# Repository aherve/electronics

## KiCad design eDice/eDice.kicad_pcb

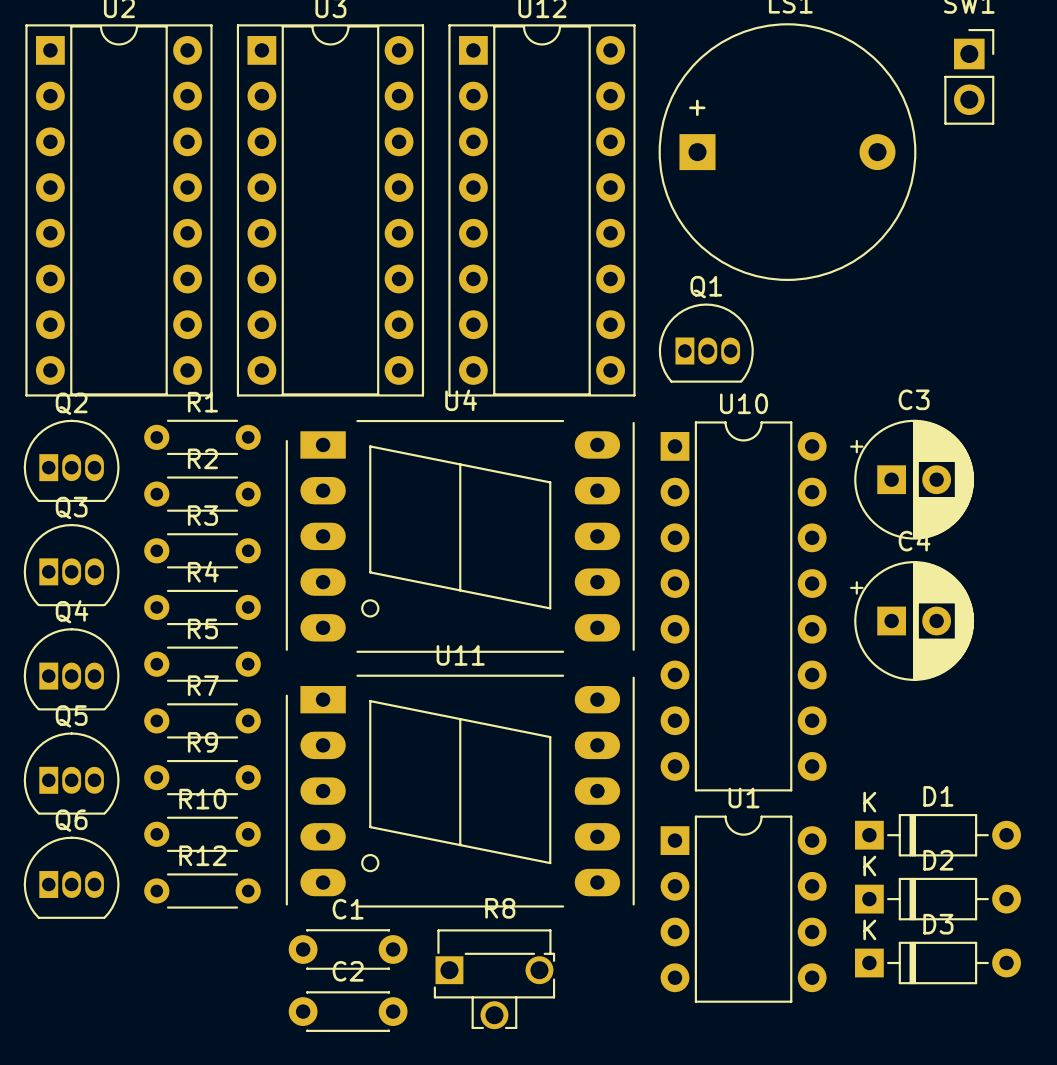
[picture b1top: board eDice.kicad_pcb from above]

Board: 2 copper layers, 32 parts (0 on the bottom side), 47 nets, no tracks yet.

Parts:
C1: 100nF; C_Disc_D4.3mm_W1.9mm_P5.00mm
C2: 10nF; C_Disc_D4.3mm_W1.9mm_P5.00mm
C3: C; CP_Radial_D6.3mm_P2.50mm
C4: C_Polarized; CP_Radial_D6.3mm_P2.50mm
D1, D2, D3: 1N4148; D_DO-35_SOD27_P7.62mm_Horizontal
LS1: buzzer; Buzzer_D14mm_H7mm_P10mm
Q1: PMOS; TO-92L_Inline
Q2, Q3, Q4, Q5, Q6: PN2222A; TO-92_Inline
R1, R2, R10: R; R_Axial_DIN0204_L3.6mm_D1.6mm_P5.08mm_Horizontal
R3: 1k; R_Axial_DIN0204_L3.6mm_D1.6mm_P5.08mm_Horizontal
R4, R5, R7, R9, R12: 10k; R_Axial_DIN0204_L3.6mm_D1.6mm_P5.08mm_Horizontal
R8: R_Variable; Potentiometer_Runtron_RM-063_Horizontal
SW1: SW_Push; PinSocket_1x02_P2.54mm_Vertical
U1: NE555P; DIP-8_W7.62mm
U2, U12: 4029; DIP-16_W7.62mm_Socket
U3: 4511; DIP-16_W7.62mm_Socket
U4, U11: SM420561N; 7SegmentLED_LTS6760_LTS6780
U10: 4511; DIP-16_W7.62mm

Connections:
GND: C1.2, C2.1, C3.2, C4.2, Q2.1 (E), R10.2, SW1.1, U1.1 (GND), U2.3 (J4), U2.4 (J1), U2.8 (VSS), U2.9 (B/D), U2.12 (J2), U2.13 (J3), U3.5 (~EL), U3.8 (Vss), U4.5 (DP), U10.5 (~EL), U10.8 (Vss), U11.5 (DP), U12.3 (J4), U12.5 (Cin), U12.8 (VSS), U12.9 (B/D), U12.12 (J2), U12.13 (J3)
unnamed: C3.1, R2.2, R3.1, SW1.2
unnamed: C4.1, LS1.2
unnamed: D1.1 (K), R2.1
unnamed: D2.2 (A), R7.1
unnamed: D2.1 (K), D3.1 (K)
unnamed: D3.2 (A), R9.1
unnamed: C1.1, Q1.1 (D), U1.2 (TR), U1.6 (THR)
unnamed: Q1.3 (S), R8.2, U1.7 (DIS)
unnamed: Q2.2 (B), R9.2
unnamed: Q2.3 (C), R1.2
unnamed: Q3.2 (B), R5.2
unnamed: Q3.3 (C), R4.2, U10.7 (DA), U12.6 (Q1)
unnamed: Q4.2 (B), R4.1
unnamed: Q4.3 (C), Q6.1 (E)
unnamed: Q4.1 (E), Q5.3 (C)
unnamed: Q5.2 (B), R7.2
unnamed: Q6.2 (B), R12.1
unnamed: Q6.3 (C), U10.6 (DD), U12.2 (Q4)
unnamed: R1.1, U4.3 (CC), U4.8 (CC)
unnamed: R10.1, U11.3 (CC), U11.8 (CC)
unnamed: C2.2, U1.5 (CV)
unnamed: U2.6 (Q1), U3.7 (DA)
unnamed: R5.1, U2.11 (Q2), U3.1 (DB)
unnamed: U2.14 (Q3), U3.2 (DC)
unnamed: U2.2 (Q4), U3.6 (DD)
unnamed: U3.13 (Qa), U4.7 (A)
unnamed: U3.12 (Qb), U4.6 (B)
unnamed: U3.11 (Qc), U4.4 (C)
unnamed: U3.10 (Qd), U4.2 (D)
unnamed: U3.9 (Qe), U4.1 (E)
unnamed: U3.15 (Qf), U4.9 (F)
unnamed: U3.14 (Qg), U4.10 (G)
unnamed: R12.2, U10.1 (DB), U12.11 (Q2)
unnamed: U10.2 (DC), U12.14 (Q3)
unnamed: U10.13 (Qa), U11.7 (A)
unnamed: U10.12 (Qb), U11.6 (B)
unnamed: U10.11 (Qc), U11.4 (C)
unnamed: U10.10 (Qd), U11.2 (D)
unnamed: U10.9 (Qe), U11.1 (E)
unnamed: U10.15 (Qf), U11.9 (F)
unnamed: U10.14 (Qg), U11.10 (G)
unnamed: U2.5 (Cin), U12.7 (Cout)
PE: Q3.1 (E), Q5.1 (E), U2.1 (PE), U12.1 (PE)
clck: D1.2 (A), LS1.1, U1.3 (Q), U2.15 (CK), U12.15 (CK)
fm: Q1.2 (G), R3.2
vcc: R8.1, U1.4 (R), U1.8 (VCC), U2.10 (U/D), U2.16 (VDD), U3.3 (~LT), U3.4 (~BI), U3.16 (Vdd), U10.3 (~LT), U10.4 (~BI), U10.16 (Vdd), U12.4 (J1), U12.10 (U/D), U12.16 (VDD)

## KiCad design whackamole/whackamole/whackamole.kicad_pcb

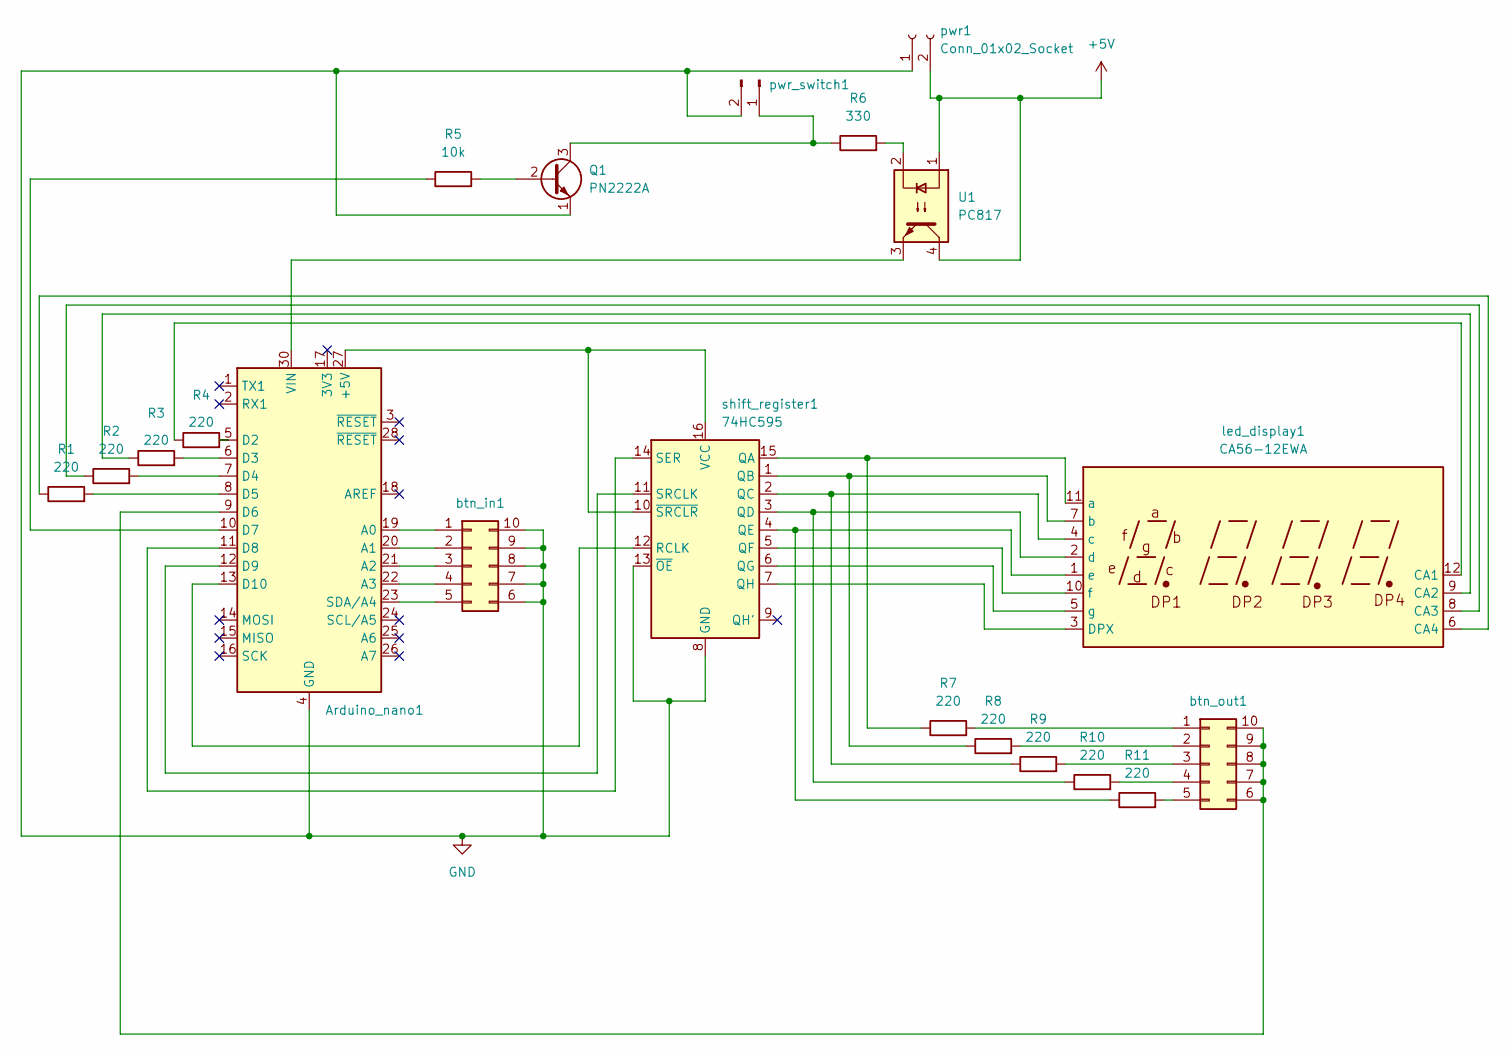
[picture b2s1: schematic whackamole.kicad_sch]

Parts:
Arduino_nano1: Arduino_Nano
Q1: PN2222A; TO-92
R1, R2, R3, R4, R7, R8, R9, R10, R11: 220; R_Axial_DIN0204_L3.6mm_D1.6mm_P1.90mm_Vertical
R5: 10k; R_Axial_DIN0207_L6.3mm_D2.5mm_P2.54mm_Vertical
R6: 330; R_Axial_DIN0204_L3.6mm_D1.6mm_P1.90mm_Vertical
U1: PC817; DIP-4_W7.62mm
btn_in1: PinHeader_2x05_P2.54mm_Vertical
btn_out1: PinHeader_2x05_P2.54mm_Vertical
led_display1: CA56-12EWA
pwr1: Conn_01x02_Socket; PinSocket_1x02_P1.27mm_Vertical
pwr_switch1: PinHeader_1x02_P2.54mm_Vertical
shift_register1: 74HC595; DIP-16_W7.62mm

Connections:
+5V: U1.1, U1.4, pwr1.2
GND: Arduino_nano1.4 (GND), Arduino_nano1.29 (GND), Q1.1 (E), btn_in1.6, btn_in1.7, btn_in1.8, btn_in1.9, btn_in1.10, pwr1.1, pwr_switch1.2, shift_register1.8 (GND), shift_register1.13 (~OE)
unnamed: Arduino_nano1.27 (+5V), shift_register1.10 (~SRCLR), shift_register1.16 (VCC)
unnamed: Arduino_nano1.19 (A0), btn_in1.1
unnamed: Arduino_nano1.20 (A1), btn_in1.2
unnamed: Arduino_nano1.21 (A2), btn_in1.3
unnamed: Arduino_nano1.22 (A3), btn_in1.4
unnamed: Arduino_nano1.5 (D2), R4.2
unnamed: Arduino_nano1.6 (D3), R3.2
unnamed: Arduino_nano1.7 (D4), R2.2
unnamed: Arduino_nano1.8 (D5), R1.2
unnamed: Arduino_nano1.9 (D6), btn_out1.6, btn_out1.7, btn_out1.8, btn_out1.9, btn_out1.10
unnamed: Arduino_nano1.10 (D7), R5.1
unnamed: Arduino_nano1.11 (D8), shift_register1.14 (SER)
unnamed: Arduino_nano1.12 (D9), shift_register1.11 (SRCLK)
unnamed: Arduino_nano1.13 (D10), shift_register1.12 (RCLK)
unnamed: Arduino_nano1.23 (SDA/A4), btn_in1.5
unnamed: Arduino_nano1.30 (VIN), U1.3
unnamed: Q1.2 (B), R5.2
unnamed: Q1.3 (C), R6.1, pwr_switch1.1
unnamed: R6.2, U1.2
unnamed: R7.2, btn_out1.1
unnamed: R8.2, btn_out1.2
unnamed: R9.2, btn_out1.3
unnamed: R10.2, btn_out1.4
unnamed: R11.2, btn_out1.5
unnamed: R4.1, led_display1.12 (CA1)
unnamed: R3.1, led_display1.9 (CA2)
unnamed: R2.1, led_display1.8 (CA3)
unnamed: R1.1, led_display1.6 (CA4)
unnamed: led_display1.3 (DPX), shift_register1.7 (QH)
unnamed: R7.1, led_display1.11 (a), shift_register1.15 (QA)
unnamed: R8.1, led_display1.7 (b), shift_register1.1 (QB)
unnamed: R9.1, led_display1.4 (c), shift_register1.2 (QC)
unnamed: R10.1, led_display1.2 (d), shift_register1.3 (QD)
unnamed: R11.1, led_display1.1 (e), shift_register1.4 (QE)
unnamed: led_display1.10 (f), shift_register1.5 (QF)
unnamed: led_display1.5 (g), shift_register1.6 (QG)

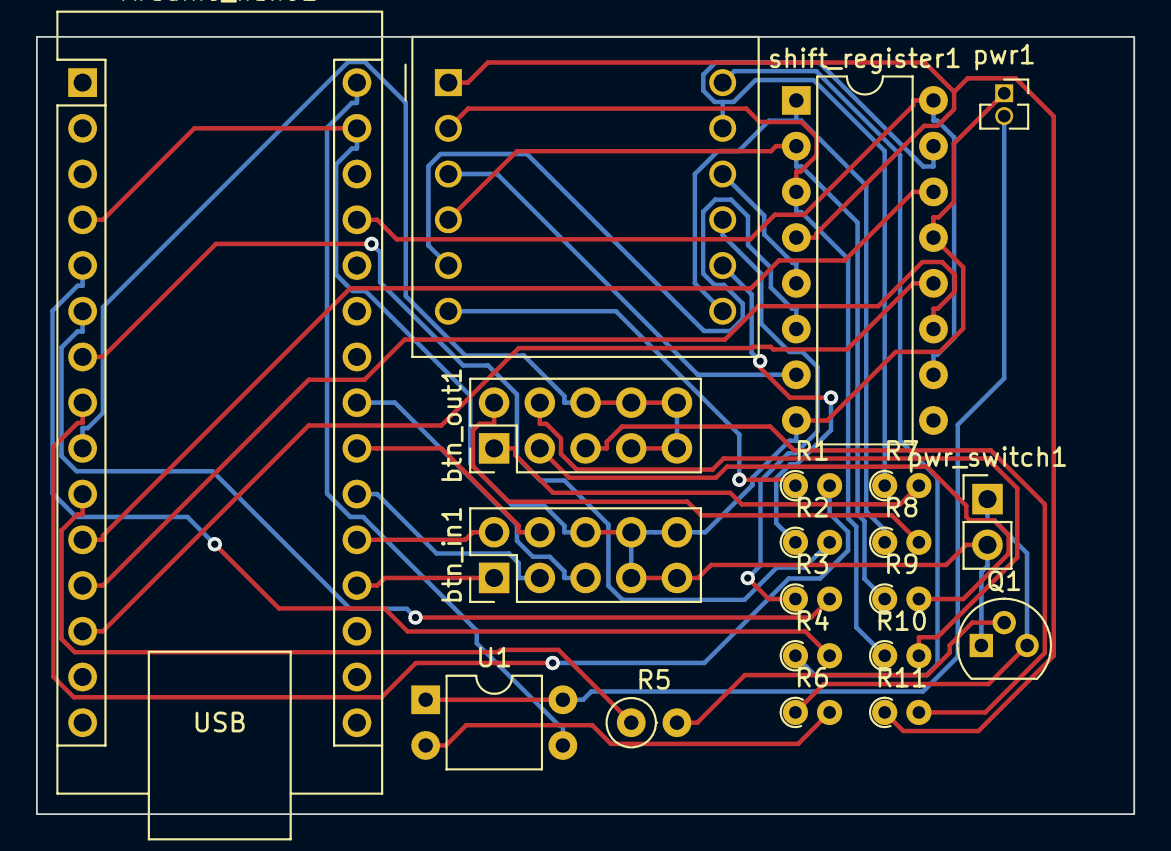
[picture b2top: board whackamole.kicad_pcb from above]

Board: 2 copper layers, 61.0 x 43.2 mm, 20 parts (0 on the bottom side), 38 nets.

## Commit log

2021-03-10 added led plug schematics
2021-03-11 simon game encoded
2021-03-11 minor fix
2021-03-13 update pin plugs
2021-03-13 add free mode
2021-03-29 added digital score display
2021-03-29 set display pins as output, + renaming
2021-03-31 fix: seed random sequence on unused pin
2024-01-03 whackamole bootstrap
2024-01-03 playing around
2024-01-03 display led state, display number
2024-01-03 moar playing around
2024-01-06 try kiCad
2024-01-07 progress, yeah
2024-01-08 sounds
2024-01-08 with sound
2024-01-13 wip save
2024-01-14 somehow functional game
2024-01-14 minor improvements
2024-01-15 start, end
2024-01-15 start and end
2024-01-16 Let's go !
2024-01-17 capacitor to regulate player tension and avoid unexpected shutdowns
2024-01-29 bam wip
2024-01-29 true latch
2024-01-30 progress
2024-01-30 remove kicad locks
2024-01-30 minor updates
2024-01-30 battery life improvements
2024-02-17 dice
2024-02-17 rename nixie edice
2024-02-17 update: d6/20
2024-02-21 edice
2024-03-21 eboard
2024-03-23 eboard wip
2024-03-25 bootstrap ino file
2024-03-25 eBoard board read
2024-03-25 testing with 797ICs
2024-03-26 cleanup
2024-03-26 spi working
2024-03-26 remove useless delay
